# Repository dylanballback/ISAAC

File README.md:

# ISAAC
Integrated Spacecraft Autonomous Attitude Controller

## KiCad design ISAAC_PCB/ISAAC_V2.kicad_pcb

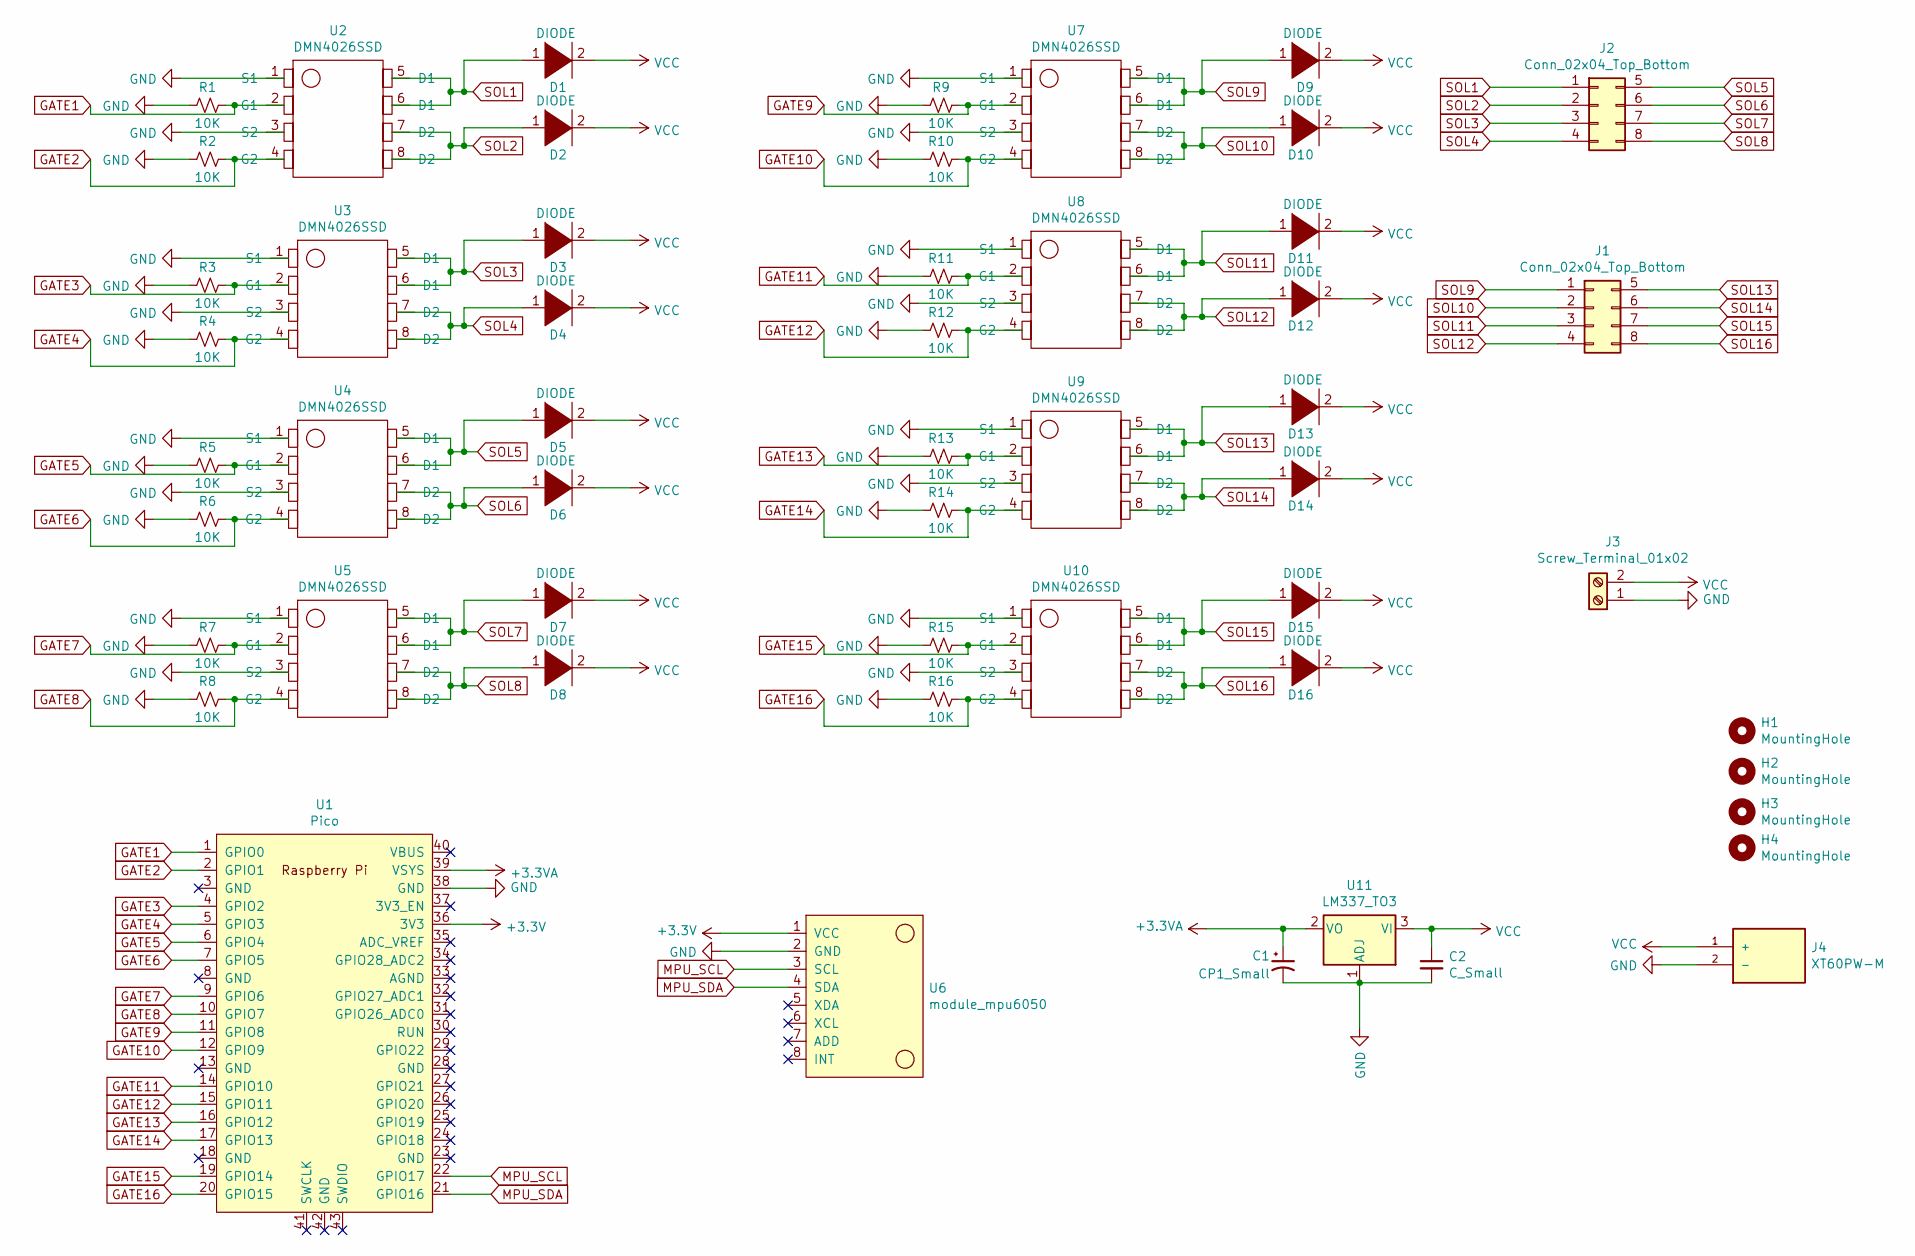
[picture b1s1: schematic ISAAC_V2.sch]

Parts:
C1: CP1_Small; CP_Radial_D4.0mm_P1.50mm
C2: C_Small; CP_Radial_D4.0mm_P1.50mm
D1, D2, D3, D4, D5, D6, D7, D8, D9, D10, D11, D12, D13, D14, D15, D16: DIODE; D_1812_4532Metric_Pad1.30x3.40mm_HandSolder
H1, H2, H3, H4: MountingHole; MountingHole_3.2mm_M3
J1, J2: Conn_02x04_Top_Bottom; Molex_Mini-Fit_Jr_5569-08A2_2x04_P4.20mm_Horizontal
J3: Screw_Terminal_01x02; TE_282837-2
J4: XT60PW-M; AMASS_XT60PW-M; PARTREV V1.2
R1, R2, R3, R4, R5, R6, R7, R8, R9, R10, R11, R12, R13, R14, R15, R16: 10K; R_0805_2012Metric_Pad1.20x1.40mm_HandSolder
U1: Pico; RPi_Pico_SMD_TH
U2, U3, U4, U5, U7, U8, U9, U10: DMN4026SSD; SOIC127P600X150-8N
U6: module_mpu6050
U11: LM337_TO3; SOT230P696X180-4N

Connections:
+3.3VA: C1.1, U1.39 (VSYS), U11.2 (VO)
+3V3: U1.36 (3V3), U6.1 (VCC)
GATE1: R1.1, U1.1 (GPIO0), U2.2 (G1)
GATE2: R2.1, U1.2 (GPIO1), U2.4 (G2)
GATE3: R3.1, U1.4 (GPIO2), U3.2 (G1)
GATE4: R4.1, U1.5 (GPIO3), U3.4 (G2)
GATE5: R5.1, U1.6 (GPIO4), U4.2 (G1)
GATE6: R6.1, U1.7 (GPIO5), U4.4 (G2)
GATE7: R7.1, U1.9 (GPIO6), U5.2 (G1)
GATE8: R8.1, U1.10 (GPIO7), U5.4 (G2)
GATE9: R9.1, U1.11 (GPIO8), U7.2 (G1)
GATE10: R10.1, U1.12 (GPIO9), U7.4 (G2)
GATE11: R11.1, U1.14 (GPIO10), U8.2 (G1)
GATE12: R12.1, U1.15 (GPIO11), U8.4 (G2)
GATE13: R13.1, U1.16 (GPIO12), U9.2 (G1)
GATE14: R14.1, U1.17 (GPIO13), U9.4 (G2)
GATE15: R15.1, U1.19 (GPIO14), U10.2 (G1)
GATE16: R16.1, U1.20 (GPIO15), U10.4 (G2)
GND: C1.2, C2.2, J3.1, J4.2 (-), R1.2, R2.2, R3.2, R4.2, R5.2, R6.2, R7.2, R8.2, R9.2, R10.2, R11.2, R12.2, R13.2, R14.2, R15.2, R16.2, U1.38 (GND), U2.1 (S1), U2.3 (S2), U3.1 (S1), U3.3 (S2), U4.1 (S1), U4.3 (S2), U5.1 (S1), U5.3 (S2), U6.2 (GND), U7.1 (S1), U7.3 (S2), U8.1 (S1), U8.3 (S2), U9.1 (S1), U9.3 (S2), U10.1 (S1), U10.3 (S2), U11.1 (ADJ)
MPU_SCL: U1.22 (GPIO17), U6.3 (SCL)
MPU_SDA: U1.21 (GPIO16), U6.4 (SDA)
SOL1: D1.1 (K), J2.1, U2.5 (D1), U2.6 (D1)
SOL2: D2.1 (K), J2.2, U2.7 (D2), U2.8 (D2)
SOL3: D3.1 (K), J2.3, U3.5 (D1), U3.6 (D1)
SOL4: D4.1 (K), J2.4, U3.7 (D2), U3.8 (D2)
SOL5: D5.1 (K), J2.5, U4.5 (D1), U4.6 (D1)
SOL6: D6.1 (K), J2.6, U4.7 (D2), U4.8 (D2)
SOL7: D7.1 (K), J2.7, U5.5 (D1), U5.6 (D1)
SOL8: D8.1 (K), J2.8, U5.7 (D2), U5.8 (D2)
SOL9: D9.1 (K), J1.1, U7.5 (D1), U7.6 (D1)
SOL10: D10.1 (K), J1.2, U7.7 (D2), U7.8 (D2)
SOL11: D11.1 (K), J1.3, U8.5 (D1), U8.6 (D1)
SOL12: D12.1 (K), J1.4, U8.7 (D2), U8.8 (D2)
SOL13: D13.1 (K), J1.5, U9.5 (D1), U9.6 (D1)
SOL14: D14.1 (K), J1.6, U9.7 (D2), U9.8 (D2)
SOL15: D15.1 (K), J1.7, U10.5 (D1), U10.6 (D1)
SOL16: D16.1 (K), J1.8, U10.7 (D2), U10.8 (D2)
VCC: C2.1, D1.2 (A), D2.2 (A), D3.2 (A), D4.2 (A), D5.2 (A), D6.2 (A), D7.2 (A), D8.2 (A), D9.2 (A), D10.2 (A), D11.2 (A), D12.2 (A), D13.2 (A), D14.2 (A), D15.2 (A), D16.2 (A), J3.2, J4.1 (+), U11.3 (VI)

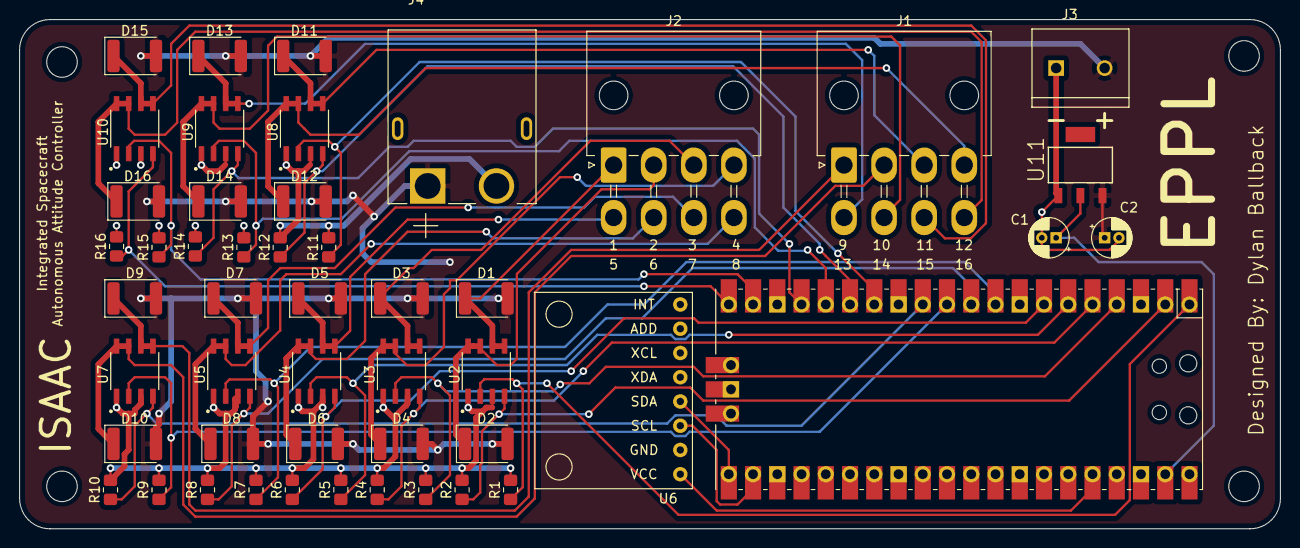
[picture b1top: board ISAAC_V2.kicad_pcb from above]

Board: 2 copper layers, 132.1 x 53.3 mm, 53 parts (0 on the bottom side), 38 nets.

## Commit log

2021-10-17 Updated Files
2021-10-17 Created Schematic
2021-10-18 Added Pico, Molex Connectors, MPU6050
2021-10-18 Added XT60 Conn and Started Tracing PCB
2021-10-18 Finished Version 1
2021-10-18 Uploaded Images For ReadME
2021-11-01 Updated everything!
2021-11-03 Updated Everything Again!
2021-11-04 Minor Changes
2021-11-08 Updated PCB and Tracing
2021-11-11 updated pcb
2021-11-14 Finished tracing PCB
2021-11-16 Fixed GND layers
